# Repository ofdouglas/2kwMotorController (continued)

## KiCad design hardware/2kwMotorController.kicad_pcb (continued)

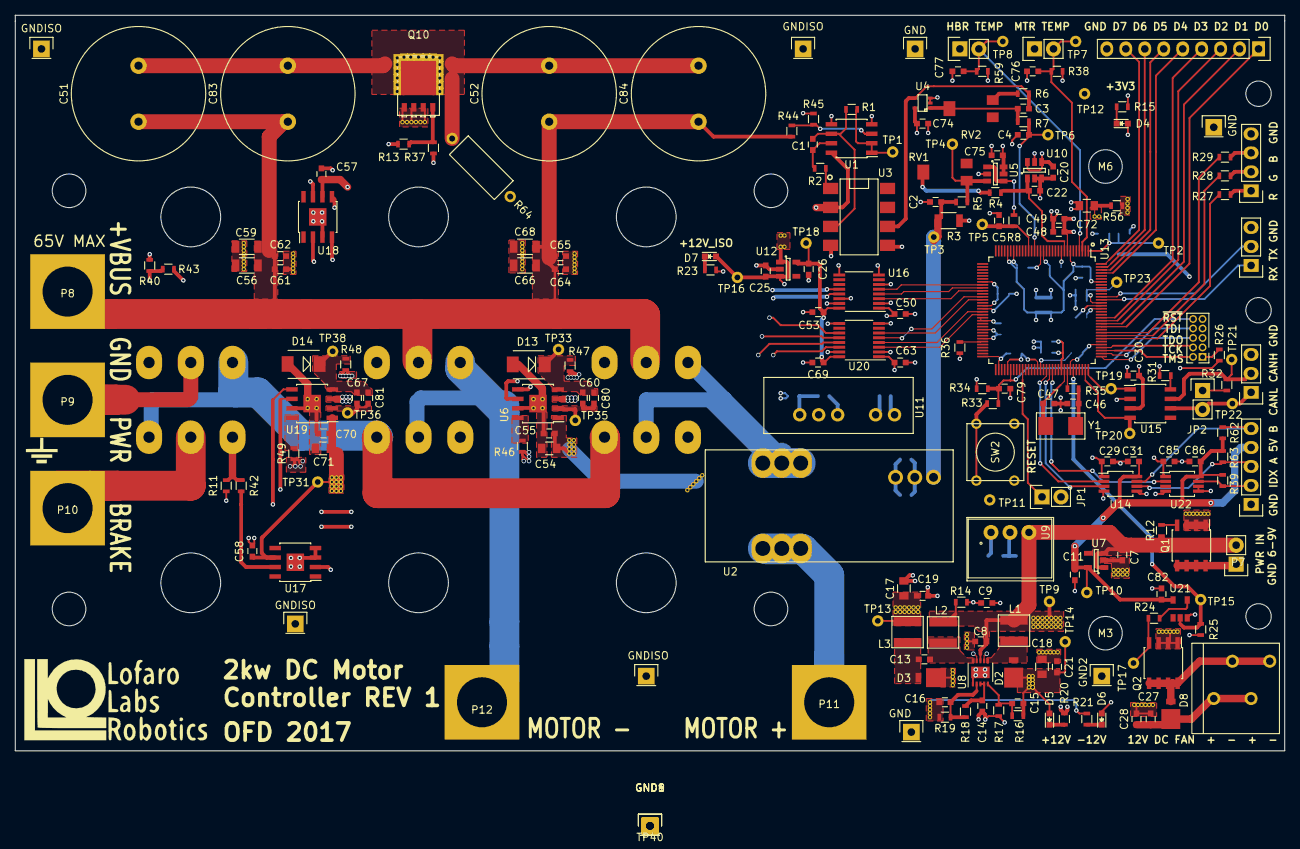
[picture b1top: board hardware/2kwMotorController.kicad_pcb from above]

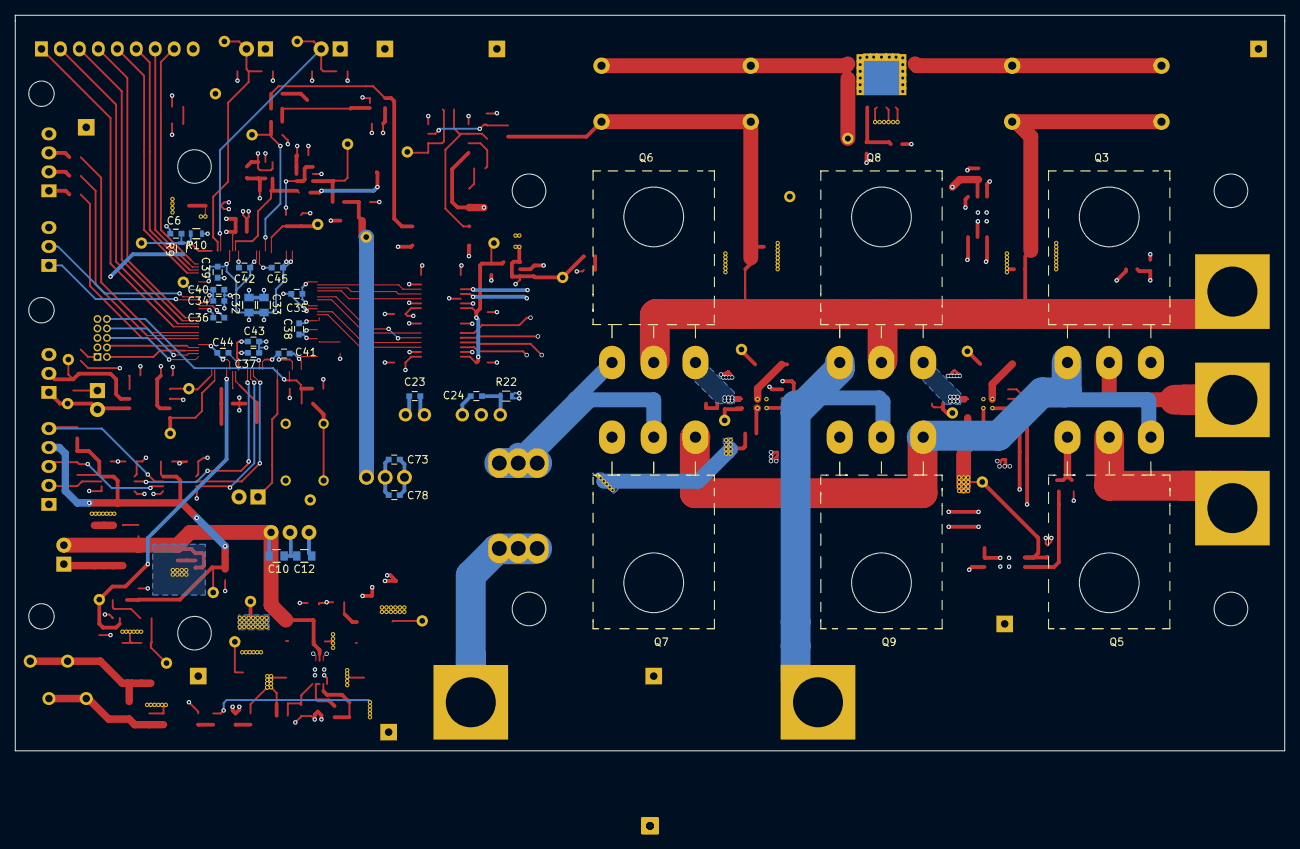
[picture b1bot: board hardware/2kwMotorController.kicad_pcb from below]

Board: 4 copper layers, 170.0 x 98.5 mm, 245 parts (30 on the bottom side), 123 nets.

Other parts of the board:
GND: GND_POINT; Pin_Header_Straight_1x01
GND#2, GND#3: GND_POINT; Pin_Header_Straight_1x01
GNDISO: GND_POINT; Pin_Header_Straight_1x01
GNDISO#2, GNDISO#3, GNDISO#4: GND_POINT; Pin_Header_Straight_1x01
M3, M6: MOUNTING_HOLE; M4-SCREW-HOLE

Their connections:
GND: GND.1, GND#2.1, GND#3.1; also elsewhere on the board
GNDPWR: GNDISO.1, GNDISO#2.1, GNDISO#3.1, GNDISO#4.1; also elsewhere on the board

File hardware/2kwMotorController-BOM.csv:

Id,Designator,Package,Quantity,Designation,Supplier and ref
1,H1,DHS-B10680-04A,1,DHS-B10680-04A,
,,,,,
3,"C51,C52",Cap_Horizontal_D18_L36,2,1m,
4,P7,TERM_5P_2-5_1990038,1,CONN_01X05_ENCODER,
5,"C29,C4,C6,C9,C14,C30,C31,C38,C39,C40,C41,C42,C43,C44,C45,C53,C57,C58,C63,C35,C36,C50,C69,C70,C74,C75,C76,C77,C73,C27,C55,C80,C81,C82",C_0603,34,100n,
6,"C56,C59,C66,C68",C_1206,4,1u,
7,U13,TQFP-128_14x14mm_Pitch0.4mm_LONG,1,TM4C1294KCPDT,
8,"U17,U18",SOIC-8-1EP_3.9x4.9mm_Pitch1.27mm,2,MIC4127,
9,R44,R_0603,1,18k,
10,"R33,R2",R_0603,2,470,
11,U2,LAH_100-P,1,LAH-100P,
12,"C1,C3,C46,C47",C_0603,4,10p,
13,C2,C_0603,1,27n,
14,C5,C_0603,1,47n,
15,"C7,C11,C13,C19,C21,C25,C26,C48,C60,C67,C37,C78,C28,C79",C_0603,14,1u,
16,C8,C_0603,1,4.7u,
17,C10,C_0603,1,10u,
18,"C16,C15",C_0603,2,56p,
19,"C20,C23,C24,C34",C_0603,4,2.2u,
20,C22,C_0603,1,300p,
21,"C49,C61,C62,C64,C65",C_0603,5,10n,
22,JP1,Pin_Header_Straight_1x02,1,Jumper_NO_Small,
23,"Q1,Q2",SOIC-8_3.9x4.9mm_Pitch1.27mm,2,DMG4712SSS,
24,"R1,R19",R_0603,2,120k,
25,"R4,R5,R14,R17,R18,R25,R34,R37,R40,R41,R59,R62,R63,R38,R11",R_0603,15,10k,
26,R6,R_0603,1,39k,
27,R7,R_0603,1,47,
28,R8,R_0603,1,33,
29,R9,R_0603,1,270k,
30,R10,R_0603,1,100k,
31,"R12,R13,R26,R39",R_0603,4,100,
32,"R15,R27,R28,R29,R30,R32",R_0603,6,120,
33,R16,R_0603,1,110k,
34,"R20,R21,R23",R_0603,3,1.8k,
35,"R22,R57,R58",R_0603,3,2.2k,
36,R24,R_0603,1,180,
37,R31,R_0603,1,0,
38,R35,R_0603,1,1k,
39,R36,R_0603,1,4.87k,
40,"R49,R42,R43,R46,R47,R48",R_0603,6,2.2,
41,Y1,NX5032GA-CRYSTAL,1,NX5032GA,
42,P1,TERM_2P_2-5_1990009,1,CONN_01X02_CBAT,
43,P6,TERM_3P_2-5_1990012,1,CONN_01X03_CAN,
44,SW2,SW_PUSH_SMALL,1,SW_PUSH,
45,"U20,U16",QSOP-16_3.9x4.9mm_Pitch0.635mm,2,Si8045AA,
46,L1,INDUCTOR_NR40xx,1,10u,
47,"L2,L3",INDUCTOR_NR40xx,2,15u,
48,P2,TERM_2P_2-5_1990009,1,CONN_01X02_FAN,
49,P4,Pin_Header_Straight_2x05_Pitch1.27mm,1,CONN_02X05_JTAG,
50,U4,SC-70-5,1,MCP6001,
51,U5,SOT-23-6,1,ADA4805-1,
52,"U7,U12",SOT-23-5,2,MIC5225-5.0,
53,U8,DFN-10-1EP_3x3mm_Pitch0.5mm,1,LT3471,
54,U10,SOT-23-6,1,MCP1501T-30E,
55,U11,PDM2-S,1,PDM1-S,
56,U15,SOIC-8_3.9x4.9mm_Pitch1.27mm,1,SN65HVD231D,
57,U3,DIP-8_SMD,1,LOC110,
58,"D2,D3",DIODE_POWERMITE,2,MBRM-120,
59,"D4,D5,D6,D7,D9,D10,D11,D12",LED_0603,8,LED,
60,D8,DIODE_POWERMITE,1,SK310-B,
61,R56,R_0603,1,1,
62,RV1,Trimpot-23B,1,100,
63,RV2,Trimpot-23B,1,36k,
64,"D13,D14",DO-214AA,2,SK310-B,
65,P5,Pin_Header_Straight_1x03,1,CONN_01X03_UART,
66,"M1,M2,M3,M4,M5,M6",M4-SCREW-HOLE,6,MOUNTING_HOLE,
67,"R64,R65",RESISTOR_FMP200,2,150,
68,P8,M6_4AWG_LUG_TERM,1,CONN_01_V+,
69,P10,M6_4AWG_LUG_TERM,1,CONN_01_BRK,
70,P9,M6_4AWG_LUG_TERM,1,CONN_01_V-,
71,P12,M6_4AWG_LUG_TERM,1,CONN_01_M-,
72,P11,M6_4AWG_LUG_TERM,1,CONN_01_M+,
73,R3,R_1206,1,59,
74,P13,TERM_2P_2-5_1990009,1,CONN_01X02_MTMP,
75,P14,TERM_2P_2-5_1990009,1,CONN_01X02_BTMP,
76,"C12,C17,C18,C32,C33,C72",C_0805,6,10u,
77,"C54,C71",C_0805,2,4.7u,
78,"U19,U6",SOIC-8-1EP_3.9x4.9mm_Pitch1.27mm,2,UCC27211,
79,R45,R_0603,1,2k,
80,P3,Pin_Header_Straight_1x09,1,CONN_01X09,
81,U1,SOIC-8_3.9x4.9mm_Pitch1.27mm,1,LM358A,
82,U14,MSOP-8_3x3mm_Pitch0.65mm,1,74LVCH2T45,
83,U21,SC-74A,1,74LVC1G17,
84,"TP1,TP2,TP3,TP4,TP5,TP6,TP7,TP8,TP9,TP10,TP11,TP12,TP13,TP14,TP15,TP16,TP17,TP18,TP19,TP20,TP21,TP22,TP23,TP31,TP33,TP35,TP36,TP38",TEST_PAD_1.27mm,28,TEST_POINT,
85,U9,R-78E-0.5,1,R-78E3.3-0.5,
86,,,,,
87,"GND,GND,GND,GND_ISO,GND_ISO,GND_ISO,GND_ISO",Pin_Header_Straight_1x01,7,GND_POINT,
88,,,,,
89,"Q10,Q4",SOT-669_LFPAK_PASTE,2,PSMN021-100,
90,"Q8,Q3,Q5,Q9,Q7,Q6",TO-247_Horizontal_Neutral123_MountFromLS_largePads,6,IRFP4468,

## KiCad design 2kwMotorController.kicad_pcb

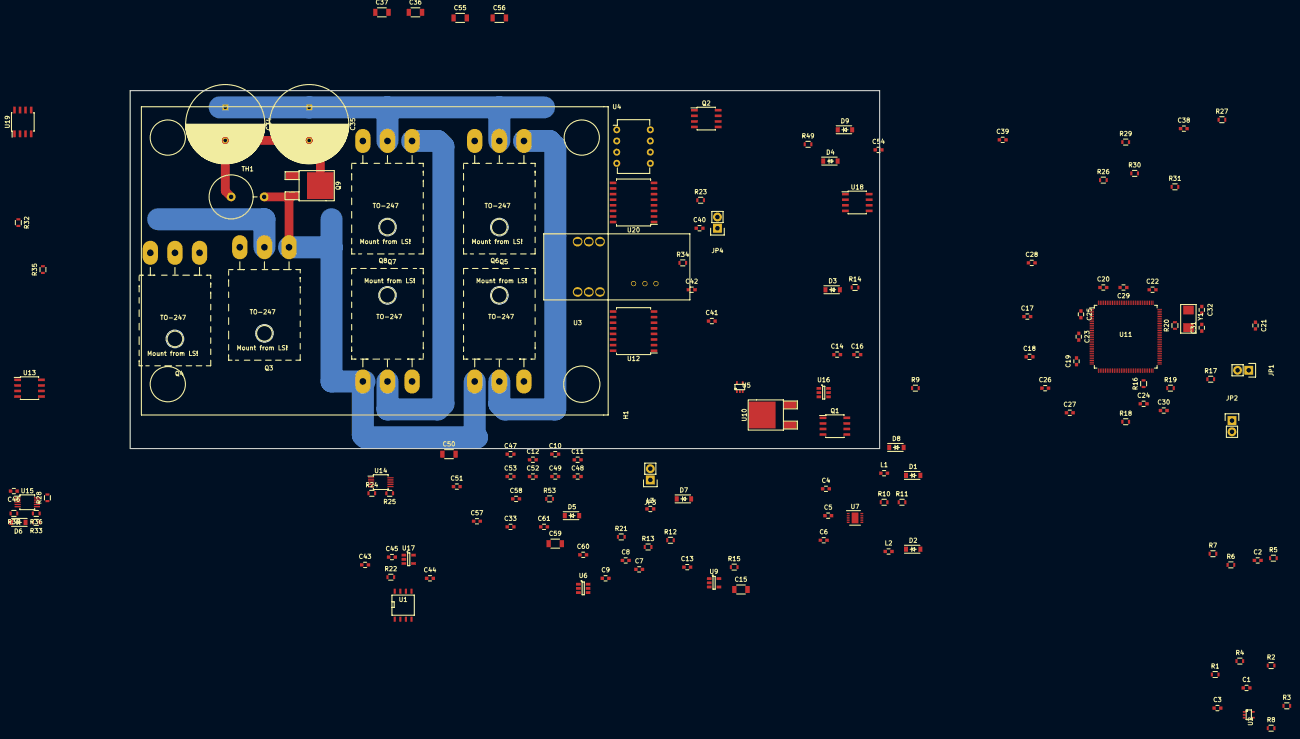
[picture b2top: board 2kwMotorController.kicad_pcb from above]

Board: 4 copper layers, 170.2 x 81.3 mm, 147 parts (0 on the bottom side), 87 nets.

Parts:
C1, C3: 47p; C_0603
C2: 27n; C_0603
C4, C7, C14, C24, C43, C44, C48, C49, C52: 1u; C_0603
C5, C10, C12: 4.7u; C_0603
C6, C8, C13, C19, C20, C22, C23, C25, C26, C27, C28, C29, C30, C38, C39, C41, C42, C45, C51, C54, C60, C61: 100n; C_0603
C9, C11: 56p; C_0603
C15, C36, C37, C55, C56: 10u; C_1206
C16, C21: 2.2u; C_0603
C17, C18, C40, C46: 10u; C_0603
C31, C32: 10p; C_0603
C33, C57, C58: 47n; C_0603
C34, C35: 1.5m; C_Radial_D18_L36_P7.5
C47: 300p; C_0603
C50: 100n; C_1206
C53: 10n; C_0603
C59: 1u; C_1206
D1, D2, D4: MBRM-120; SOD-123
D3, D5, D8, D9: LED; SOD-123
D6, D7: S210F; SOD-123
H1: DHS-B10680-04A
JP1, JP2, JP3, JP4: Jumper_NO_Small; Pin_Header_Straight_1x02
L1, L2, L3: 10u; C_0603
Q1, Q2: DMG4712SSS; SOIC-8_3.9x4.9mm_Pitch1.27mm
Q3, Q4, Q5, Q6, Q7, Q8: IRFP4468; TO-247_Horizontal_Neutral123_MountFromLS_largePads
Q9: DMT10H010LK3; TO-252-2Lead
R1: 270k; R_0603
R2: 100k; R_0603
R3: 1.2M; R_0603
R4, R18: 470; R_0603
R5: 59.0; R_0603
R6, R7, R11, R12, R15, R19, R24, R25, R26, R27, R28, R29, R30, R31, R36, R37, R53: 10k; R_0603
R8: 39k; R_0603
R9, R17: 100; R_0603
R10: 110k; R_0603
R13: 120k; R_0603
R14: 1.8k; R_0603
R16: 4.87k; R_0603
R20: 1k; R_0603
R21: 1; R_0603
R22, R23, R32, R33, R34, R35, R49: 2.2; R_0603
TH1: B57127P100M301; Resistor_Vertical_RM7.5mm
U1: LM358; SOIC-8-N
U2, U5: MCP6001; SC-70-5
U3: LAH-100P; LAH_100-P
U4: LOC110; DIP-8_W7.62mm
U6: ADA4805-1; SOT-23-6
U7: LT3471; DFN-10-1EP_3x3mm_Pitch0.5mm
U9, U17: MIC5225-5.0; SOT-23-5
U10: LF33ABDT; TO-252-2Lead
U11: TM4C1294KCPDT; TQFP-128_14x14mm_Pitch0.4mm
U12, U20: Si8640; SOIC-16_7.5x10.3mm_Pitch1.27mm
U13, U19: MIC4127; SOIC-8_3.9x4.9mm_Pitch1.27mm
U14, U15: LM5102; MSOP-10_3x3mm_Pitch0.5mm
U16: MCP1501T-30E; SOT-23-6
U18: SN65HVD231D; SOIC-8_3.9x4.9mm_Pitch1.27mm
Y1: NX5032GA; NX5032GA-CRYSTAL

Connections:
+3.3VADC: U2.2, U5.5, U6.5, U6.6
+3V3: C15.1, C16.1, C17.1, C18.1, C19.1, C20.1, C22.1, C23.1, C25.1, C26.1, C28.1, C29.1, C38.1, C47.1, C51.1, C52.1, C53.1, C60.1, D4.2, D5.2, R6.2, R17.1, R19.1, U10.3, U11.7, U11.8, U11.9, U11.16, U11.26, U11.28, U11.39, U11.47, U11.51, U11.52, U11.69, U11.79, U11.90, U11.101, U11.113, U11.122, U12.1, U16.1, U16.4, U16.6, U18.3, U20.1
+5V: C14.1, U9.5
+5V_ISO: C39.1, C49.1, C61.1, JP3.1, JP4.1, U12.16, U17.5, U20.16
+12V: C9.1, C12.1, C50.1, C59.1, D1.1, D8.2, R10.1, U3.4
+12V_ISO: C40.1, C41.1, C42.1, C45.1, C46.1, C48.1, C54.1, D3.2, U1.8, U4.2, U13.6, U14.1, U15.1, U17.1, U17.3, U19.6
+BATT: C4.1, C5.1, C13.1, D4.1, L1.1, L2.1, R9.1, R15.2, U7.8, U9.1, U9.3, U10.1
-12V: C10.2, C11.1, L3.2, R13.2, U3.3
/h-bridge/BRAKE: Q4.2, R21.2
/h-bridge/I_SENSE+: Q5.3, Q6.2, R33.1, U3.1
/h-bridge/M-: Q7.3, Q8.2, R34.1
/h-bridge/PWM1_GD: R31.1, U14.7, U20.14
/h-bridge/PWM1_MCU: U11.44, U20.3
/h-bridge/PWM2_GD: R30.1, U14.8, U20.13
/h-bridge/PWM2_MCU: U11.45, U20.4
/h-bridge/PWM3_GD: R29.1, U15.7, U20.12
/h-bridge/PWM3_MCU: U11.50, U20.5
/h-bridge/PWM4_GD: R28.1, U15.8, U20.11
/h-bridge/PWM4_MCU: U11.49, U20.6
/h-bridge/VBUS: C34.1, C35.1, C36.1, C37.1, C55.1, C56.1, Q5.2, Q7.2, R3.2, R21.1
/h-bridge/VBUS_DIS_GD: R27.1, U12.13, U13.2
/h-bridge/VBUS_DIS_MCU: U11.63, U12.4
/h-bridge/VBUS_EN_GD: R26.1, U12.12, U19.2
/h-bridge/VBUS_EN_MCU: U11.71, U12.5
/h-bridge/VBUS_ST_GD: R53.1, U12.14, U13.4
/mcu/CAN_ID_0: JP1.2, U11.78
/mcu/CAN_ID_1: JP2.2, U11.77
/mcu/CAN_RX: U11.95, U18.4
/mcu/CAN_TX: U11.96, U18.1
/mcu/I_SENSOR_OUT: C57.1, U11.125
/mcu/JTAG_RST_N: R19.2, U11.70
/mcu/VBAT_CTRL: C58.1, U11.126
/mcu/VBUS_MOTOR: C33.1, U11.127
GND: C2.2, C4.2, C5.2, C6.2, C8.1, C10.1, C12.2, C13.2, C15.2, C17.2, C18.2, C19.2, C20.2, C21.2, C22.2, C23.2, C24.2, C25.2, C26.2, C27.2, C28.2, C29.2, C30.2, C31.2, C32.2, C33.2, C38.2, C50.2, C51.2, C57.2, C58.2, C59.2, C60.2, D2.1, D9.2, JP1.1, JP2.1, Q1.1, Q1.2, Q1.3, Q2.1, Q2.2, Q2.3, R2.2, R5.2, R11.1, R16.1, R18.2, U1.3, U2.5, U4.5, U5.2, U5.3, U6.2, U7.5, U7.11, U9.2, U10.2, U11.17, U11.48, U11.55, U11.58, U11.64, U11.66, U11.80, U11.114, U12.2, U12.6, U12.8, U18.2, U20.2, U20.8
GNDA: C47.2, C52.2, C53.2, U11.10
GNDCBAT: Q1.5, Q1.6, Q1.7, Q1.8
GNDPWR: C14.2, C36.2, C37.2, C39.2, C40.2, C41.2, C42.2, C45.2, C46.2, C48.2, C49.2, C54.2, C55.2, C56.2, C61.2, D6.2, D7.2, Q3.3, Q4.3, Q6.3, Q8.3, Q9.3, R14.2, R24.2, R25.2, R26.2, R27.2, R28.2, R29.2, R30.2, R31.2, R36.2, R37.2, R53.2, TH1.2, U1.4, U4.4, U12.9, U12.15, U13.3, U14.9, U15.9, U17.2, U19.3, U19.4, U20.9, U20.15
unnamed: C1.1, R4.2, U1.1
unnamed: C1.2, R3.1, U1.2, U4.3
unnamed: C2.1, R5.1, R7.2, U3.5
unnamed: C3.1, U5.1
unnamed: C3.2, R8.2, U4.6, U5.4
unnamed: C6.1, R15.1, U7.7, U7.9
unnamed: C7.1, D2.2, L3.1
unnamed: C7.2, L2.2, U7.6
unnamed: C8.2, R12.1, U7.2, U7.3
unnamed: C9.2, R10.2, R11.2, U7.1
unnamed: C11.2, R12.2, R13.1, U7.4
unnamed: C16.2, U16.5
unnamed: C21.1, C24.1, C27.1, C30.1, U11.87, U11.115
unnamed: C31.1, R20.1, Y1.2
unnamed: C32.1, U11.88, Y1.1
unnamed: C34.2, C35.2, Q9.2, TH1.1
unnamed: C43.1, U14.2
unnamed: C43.2, D6.1, R33.2, U14.4
unnamed: C44.1, U15.2
unnamed: C44.2, D7.1, R34.2, U15.4
unnamed: D1.2, L1.2, U7.10
unnamed: D3.1, R14.1
unnamed: Q2.5, Q2.6, Q2.7, Q2.8
unnamed: JP3.2, U12.10
unnamed: JP4.2, U20.10
unnamed: Q1.4, R9.2
unnamed: Q3.1, R49.2
unnamed: Q4.1, R23.2
unnamed: Q5.1, U14.3
unnamed: Q6.1, R32.1
unnamed: Q7.1, U15.3
unnamed: Q8.1, R35.1
unnamed: Q9.1, R22.2
unnamed: R1.2, R2.1, U2.3
unnamed: R4.1, U4.1
unnamed: R7.1, U6.3
unnamed: R16.2, U11.59
unnamed: R20.2, U11.89
unnamed: R22.1, U13.5
unnamed: R23.1, U13.7
unnamed: R24.1, U14.5
unnamed: R25.1, U14.6
unnamed: R32.2, U14.10
unnamed: R35.2, U15.10
unnamed: R36.1, U15.6
unnamed: R37.1, U15.5
unnamed: R49.1, U19.7
unnamed: U6.1, U6.4
unnamed: U2.1, U2.4
unnamed: U16.2, U16.3

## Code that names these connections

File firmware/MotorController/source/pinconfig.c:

/*
 * pinconfig.c - Configure pins based on the build target specified in build.h
 *
 *  Created on: Oct 18, 2017
 *      Author: Oliver Douglas
 */

/* T5CCP0 is used for PWM fan
 * All other timers are free for our use
 */

#include "stdinclude.h"
#include "inc/hw_gpio.h"
#include "inc/hw_memmap.h"
#include "inc/hw_types.h"
#include "driverlib/gpio.h"

// File index for ASSERT() macro
FILENUM(8)

void pinconfig(void)
{
#if BUILD_TARGET == FOO

#elif BUILD_TARGET == BUILD_TARGET_LAUNCHPAD

    MAP_SysCtlPeripheralEnable(SYSCTL_PERIPH_GPIOA);
    MAP_SysCtlPeripheralEnable(SYSCTL_PERIPH_GPIOE);
    MAP_SysCtlPeripheralEnable(SYSCTL_PERIPH_GPIOF);
    MAP_SysCtlPeripheralEnable(SYSCTL_PERIPH_GPION);

    /* Configure log UART pins:
     *  UART0RX = PA0
     *  UART0TX = PA1
     */
    MAP_GPIOPinConfigure(GPIO_PA0_U0RX);
    MAP_GPIOPinConfigure(GPIO_PA1_U0TX);
    MAP_GPIOPinTypeUART(GPIO_PORTA_BASE, GPIO_PIN_0);
    MAP_GPIOPinTypeUART(GPIO_PORTA_BASE, GPIO_PIN_1);

    /* Configure ADC test pins:
     *  AIN3 = PE0
     */
     MAP_GPIOPinTypeADC(GPIO_PORTE_BASE, GPIO_PIN_3);

    /* Configure status LED pins:
     *  PN1 = LED0
     *  PN0 = LED1
     *  PF4 = LED2
     *  PF0 = LED3
     */
     MAP_GPIOPinTypeGPIOOutput(GPIO_PORTN_BASE, GPIO_PIN_0);
     MAP_GPIOPinTypeGPIOOutput(GPIO_PORTN_BASE, GPIO_PIN_1);
     MAP_GPIOPinTypeGPIOOutput(GPIO_PORTF_BASE, GPIO_PIN_0);
     MAP_GPIOPinTypeGPIOOutput(GPIO_PORTF_BASE, GPIO_PIN_4);


#elif BUILD_TARGET == BUILD_TARGET_2KWMC_R0

    // Enable Peripheral Clocks
    MAP_SysCtlPeripheralEnable(SYSCTL_PERIPH_GPIOA);
    MAP_SysCtlPeripheralEnable(SYSCTL_PERIPH_GPIOB);
    MAP_SysCtlPeripheralEnable(SYSCTL_PERIPH_GPIOD);
    MAP_SysCtlPeripheralEnable(SYSCTL_PERIPH_GPIOF);
    MAP_SysCtlPeripheralEnable(SYSCTL_PERIPH_GPIOG);
    MAP_SysCtlPeripheralEnable(SYSCTL_PERIPH_GPIOJ);
    MAP_SysCtlPeripheralEnable(SYSCTL_PERIPH_GPIOK);
    MAP_SysCtlPeripheralEnable(SYSCTL_PERIPH_GPIOL);
    MAP_SysCtlPeripheralEnable(SYSCTL_PERIPH_GPIOM);
    MAP_SysCtlPeripheralEnable(SYSCTL_PERIPH_GPION);
    MAP_SysCtlPeripheralEnable(SYSCTL_PERIPH_GPIOP);

    /* Configure PWM Pins:
     *  M0PWM0 = PF0 (42): VBUS_DIS_MCU
     *  M0PWM2 = PF2 (44): PWM1_MCU
     *  M0PWM3 = PF3 (45): PWM2_MCU
     *  M0PWM4 = PG0 (49): PWM4_MCU
     *  M0PWM5 = PG1 (50): PWM3_MCU
     */
    MAP_GPIOPinConfigure(GPIO_PF0_M0PWM0);
    MAP_GPIOPinConfigure(GPIO_PF2_M0PWM2);
    MAP_GPIOPinConfigure(GPIO_PF3_M0PWM3);
    MAP_GPIOPinConfigure(GPIO_PG0_M0PWM4);
    MAP_GPIOPinConfigure(GPIO_PG1_M0PWM5);
    MAP_GPIOPinTypePWM(GPIO_PORTF_BASE, GPIO_PIN_0);
    MAP_GPIOPinTypePWM(GPIO_PORTF_BASE, GPIO_PIN_2);
    MAP_GPIOPinTypePWM(GPIO_PORTF_BASE, GPIO_PIN_3);
    MAP_GPIOPinTypePWM(GPIO_PORTG_BASE, GPIO_PIN_0);
    MAP_GPIOPinTypePWM(GPIO_PORTG_BASE, GPIO_PIN_1);

    /* Configure ADC pins:
     *  AIN12 = PD3 ( 4): BRIDGE_TEMP
     *  AIN13 = PD2 ( 3): MOTOR_TEMP
     *  AIN15 = PD0 ( 1): VBAT_CTRL
     *  AIN17 = PK1 (19): VBUS_MOTOR
     *  AIN19 = PK3 (21): I_SENSOR_OUT
     */
    MAP_GPIOPinTypeADC(GPIO_PORTD_BASE, GPIO_PIN_0);
    MAP_GPIOPinTypeADC(GPIO_PORTD_BASE, GPIO_PIN_2);
    MAP_GPIOPinTypeADC(GPIO_PORTD_BASE, GPIO_PIN_3);
    MAP_GPIOPinTypeADC(GPIO_PORTK_BASE, GPIO_PIN_1);
    MAP_GPIOPinTypeADC(GPIO_PORTK_BASE, GPIO_PIN_3);

    /* Configure CAN pins:
     *  CAN1RX = PB0 (95): CAN1_RX
     *  CAN1TX = PB1 (96): CAN1_TX
     */
    //
    MAP_GPIOPinConfigure(GPIO_PB0_CAN1RX);
    MAP_GPIOPinConfigure(GPIO_PB1_CAN1TX);
    MAP_GPIOPinTypeCAN(GPIO_PORTB_BASE, GPIO_PIN_0);
    MAP_GPIOPinTypeCAN(GPIO_PORTB_BASE, GPIO_PIN_1);

    /* Configure Debug pins:
     *  PN0 (107): DEBUG_0
     *  PN1 (108): DEBUG_1
     *  PN2 (109): DEBUG_2
     *  PN3 (110): DEBUG_3
     *  PD4 (125): DEBUG_4
     *  PD5 (126): DEBUG_5
     *  PD6 (127): DEBUG_6
     *  PD7 (128): DEBUG_7
     */
    MAP_GPIOPinTypeGPIOOutput(GPIO_PORTN_BASE, GPIO_PIN_0);
    MAP_GPIOPinTypeGPIOOutput(GPIO_PORTN_BASE, GPIO_PIN_1);
    MAP_GPIOPinTypeGPIOOutput(GPIO_PORTN_BASE, GPIO_PIN_2);
    MAP_GPIOPinTypeGPIOOutput(GPIO_PORTN_BASE, GPIO_PIN_3);
    MAP_GPIOPinTypeGPIOOutput(GPIO_PORTD_BASE, GPIO_PIN_4);
    MAP_GPIOPinTypeGPIOOutput(GPIO_PORTD_BASE, GPIO_PIN_5);
    MAP_GPIOPinTypeGPIOOutput(GPIO_PORTD_BASE, GPIO_PIN_6);

    // Use of PD7 requires unlock, since it can be used for NMI.
    HWREG(GPIO_PORTD_BASE+GPIO_O_LOCK) = GPIO_LOCK_KEY;
    HWREG(GPIO_PORTD_BASE+GPIO_O_CR)   |= GPIO_PIN_7;
    HWREG(GPIO_PORTD_BASE+GPIO_O_LOCK) = 0x0;
    MAP_GPIOPinTypeGPIOOutput(GPIO_PORTD_BASE, GPIO_PIN_7);

    /* Configure LED pins:
     *  PP2 (103): LED_0
     *  PP3 (104): LED_1
     *  PP4 (105): LED_2
     *  PP5 (106): LED_3
     */
    MAP_GPIOPinTypeGPIOOutput(GPIO_PORTP_BASE, GPIO_PIN_2);
    MAP_GPIOPinTypeGPIOOutput(GPIO_PORTP_BASE, GPIO_PIN_3);
    MAP_GPIOPinTypeGPIOOutput(GPIO_PORTP_BASE, GPIO_PIN_4);
    MAP_GPIOPinTypeGPIOOutput(GPIO_PORTP_BASE, GPIO_PIN_5);

    /* Configure H-Bridge control pins:
     *  PA6 (40): VBUS_EN_MCU
     *  PA7 (41): VBUS_ST_MCU
     */
    MAP_GPIOPinTypeGPIOOutput(GPIO_PORTA_BASE, GPIO_PIN_6);
    MAP_GPIOPinTypeGPIOOutput(GPIO_PORTA_BASE, GPIO_PIN_7);

    /* Configure CAN ID pins:
     *  PM0 (78): CAN_ID_0
     *  PM1 (77): CAN_ID_1
     */
    MAP_GPIOPinTypeGPIOInput(GPIO_PORTM_BASE, GPIO_PIN_0);
    MAP_GPIOPinTypeGPIOInput(GPIO_PORTM_BASE, GPIO_PIN_1);
    MAP_GPIOPadConfigSet(GPIO_PORTM_BASE, GPIO_PIN_0, GPIO_STRENGTH_2MA,
                         GPIO_PIN_TYPE_STD_WPU);
    MAP_GPIOPadConfigSet(GPIO_PORTM_BASE, GPIO_PIN_1, GPIO_STRENGTH_2MA,
                         GPIO_PIN_TYPE_STD_WPU);

    /* Configure Factory Reset pin:
     *  PM4 (74): FRST
     */
    MAP_GPIOPinTypeGPIOInput(GPIO_PORTM_BASE, GPIO_PIN_4);
    MAP_GPIOPadConfigSet(GPIO_PORTM_BASE, GPIO_PIN_4, GPIO_STRENGTH_2MA,
                         GPIO_PIN_TYPE_STD_WPU);

    /* Configure fan PWM pin:
     *  T5CCP0 = PB2 (91): PWM_FAN
     */
    MAP_GPIOPinTypeGPIOOutput(GPIO_PORTB_BASE, GPIO_PIN_2);

    /* Configure log UART pins:
     *  UART3RX = PJ0 (116): MCU_UART3_RX
     *  UART3TX = PJ1 (117): MCU_UART3_TX
     */
    MAP_GPIOPinConfigure(GPIO_PJ0_U3RX);
    MAP_GPIOPinConfigure(GPIO_PJ1_U3TX);
    MAP_GPIOPinTypeUART(GPIO_PORTJ_BASE, GPIO_PIN_0);
    MAP_GPIOPinTypeUART(GPIO_PORTJ_BASE, GPIO_PIN_1);

    /* Configure QEI pins:
     *  QEI0PHA = PL1 (82): QEI_PHA
     *  QEI0PHB = PL2 (83): QEI_PHB
     *  QEI0IDX = PL3 (84): QEI_IDX
     */
    MAP_GPIOPinConfigure(GPIO_PL1_PHA0);
    MAP_GPIOPinConfigure(GPIO_PL2_PHB0);
    MAP_GPIOPinConfigure(GPIO_PL3_IDX0);
    MAP_GPIOPinTypeQEI(GPIO_PORTL_BASE, GPIO_PIN_1);
    MAP_GPIOPinTypeQEI(GPIO_PORTL_BASE, GPIO_PIN_2);
    MAP_GPIOPinTypeQEI(GPIO_PORTL_BASE, GPIO_PIN_3);

#endif
}

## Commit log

2017-08-13 HW: change tm4c1294ncpdt to kcpdt; change LT3487 to 3471
2017-08-17 cleaned up h-bridge; added digital isolators
2017-08-17 improved inrush limiter, isolator, added aux. gate drive
2017-08-19 Added MCU pinmux file
2017-08-21 added MCU caps, reset, jtag, crystal
2017-08-21 ERC cleanup, begin pcbnew population
2017-08-23 hw: minor tweaks
2017-08-27 Begin tracking notes and simulations
2017-09-01 Improved current sensor and simplified power supplies
2017-09-04 Chose components and simulated LT3471
2017-09-07 Finish MCU HW draft 1; adjust sensors for 3v ref
2017-09-12 Update sensors, hbridge caps, add heatsink
2017-09-13 Layout first draft
2017-09-14 revised power layout
2017-09-16 Added most footprints, did non-power layout
2017-09-16 H-bridge decoupling, footprints, mechanical
    - Finished H-bridge decoupling study and chose H-bridge caps
    - Changed LT3471 inductors to those found in reference design,
    made footprints for them
    - Swapped Si86xx isolator for Si80xx (smaller package)
    - Updated heatsink footprint with correct screw sizes
    - Created mechanical hole footprints (M3, M4 screws)
2017-09-17 Bulk cap layout, diodes, lugs, leds, trimpots
    - Moved H-bridge bulk capacitors to horizontal layout
    - Changed H-bridge and fan diodes to 100V schottky
    - Made 4AWG lug mount footprint, added lugs to BOM
    - Tweaked LED resistor values, added LEDs to BOM
    - Made trimpot footprint, added trimpots to BOM
    - Added snubber to ferrite bead circuit; also added FB to BOM
2017-09-17 Inrush circuit, mounting hole position, temp sensor
    - Split inrush circuit (one for each bulk cap). Replaced NTC
    thermistor with 2W power resistor. Replaced D2Pak MOSFET with
    LFPAK MOSFETs.
    - Approximate position of mechanical holes chosen.
    - Added thermistor temp sensor circuits.
2017-09-18 High amp routes, sensors
    - Adjusted high current routing to improve clearances. Recommend
    3mm high busbar to compensate for reduced busbar width to 2mm.
    - Shrank TO-247 pads by 1mm (lengthwise) to improve busbar clearance.
    - Removed unecessary buffers / SAR ADC drive circuits from low-bandwidth
    sensors.
2017-09-18 Draft layout of controller section
2017-09-22 Gate driver layout mostly complete
    - Gate driver layout
    - Switch LM5102 for UCC27211 (higher current, more robust)
    - Tweak gate drive circuit passives
    - No soldermask on high-current traces
    - Fix error in orientation of LAH-100P footprint
    - Improved draft layout of control section
2017-09-23 more layout progress
2017-09-24 All routing finished
2017-09-24 layout cleanup, add buffer for fan drive
2017-09-25 All DRC/ERC passed
2017-09-25 tweaks, testpoints, decluttering
2017-09-26 Rev 0 board finished and submitted for manufacture
2017-09-28 Create and verify full Digikey BOM
2017-10-02 Software architecture first draft
2017-10-03 Firmware started; logging task finished
2017-10-20 Rev 0 Board Bring-Up Started
    PCB mostly assembled; errors noted in notes/rev0-mistakes.
    Logging task and status LED features tested on-board.
    Stubs for control and sensor code written, partially filled in.
2017-11-04 Open Loop Test Code
    Rough version of control task for open loop testing of H-bridge
    Rough version of sensor code
2017-11-09 basic velocity controller added
2017-11-12 Commit before starting PCB Rev 1 changes
2017-11-13 Revised layout mostly complete
2017-11-14 Rev 1 layout finished
2017-11-17 minor hw changes to submit PCB Rev 1
2017-11-17 Added CAN driver, draft of config/sys regs
2017-11-18 CAN driver and basic Python interface working
2017-11-19 Bug fixes and tweaks in firmware and python interface
2017-11-20 Rewrote command definition / parser for python interface
2017-11-21 Sensor firmware refactor, bugfixes
2017-11-22 basic RPi PWM read
2017-11-27 Bugfixes and python terminal display
2017-11-30 more tweaks
2017-12-03 Update BOM
2017-12-03 Fix update BOM commit
2017-12-03 cleanup & add gerbers
